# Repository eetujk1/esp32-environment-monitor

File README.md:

# ESP32 Environment Monitor

A custom-designed environmental monitoring board based on the ESP32-WROOM-32E-N4.

The goal of this project is to build a compact device for monitoring room temperature and relative humidity, with the possibility of expanding it into a Wi-Fi-connected monitoring system.

## Overview

The PCB integrates the main controller, sensor interface, USB programming circuitry, and power regulation into a single board.

## PCB Design

### 3D View

### PCB Layout

## Hardware

* **MCU:** ESP32-WROOM-32E-N4
* **Sensor:** DHT20
* **USB-to-UART:** CH340C
* **Voltage regulator:** AP2112K-3.3
* **Power input:** USB-C, 5 V
* **Programming:** Automatic boot mode selection with BOOT and RESET buttons
* **Sensor interface:** I²C

## Design Goals

* Custom PCB design and assembly
* Reliable temperature and humidity measurements
* Simple USB-based firmware development
* Wi-Fi connectivity for future monitoring applications
* Expandable hardware and firmware architecture

## Development Status

| Area                         | Status         |
| ---------------------------- | -------------- |
| PCB design                   | Completed      |
| PCB assembly                 | Pending        |
| Firmware                     | In development |
| Sensor validation            | Pending        |

## Planned Development

1. Bring up the hardware and verify the 3.3 V power rail.
2. Test USB communication and ESP32 firmware uploading.
3. Implement DHT20 sensor readings over I²C.
4. Validate temperature and humidity measurements.
5. Explore Wi-Fi monitoring and data visualization.

## Repository Structure

```text
esp32-environment-monitor/
├── hardware/       # PCB and schematic files
├── firmware/       # ESP32 source code
├── docs/           # Design notes and documentation
└── README.md
```

## Project Notes

This project is currently in the hardware bring-up stage. Firmware, measurements, and additional documentation will be added as development progresses.

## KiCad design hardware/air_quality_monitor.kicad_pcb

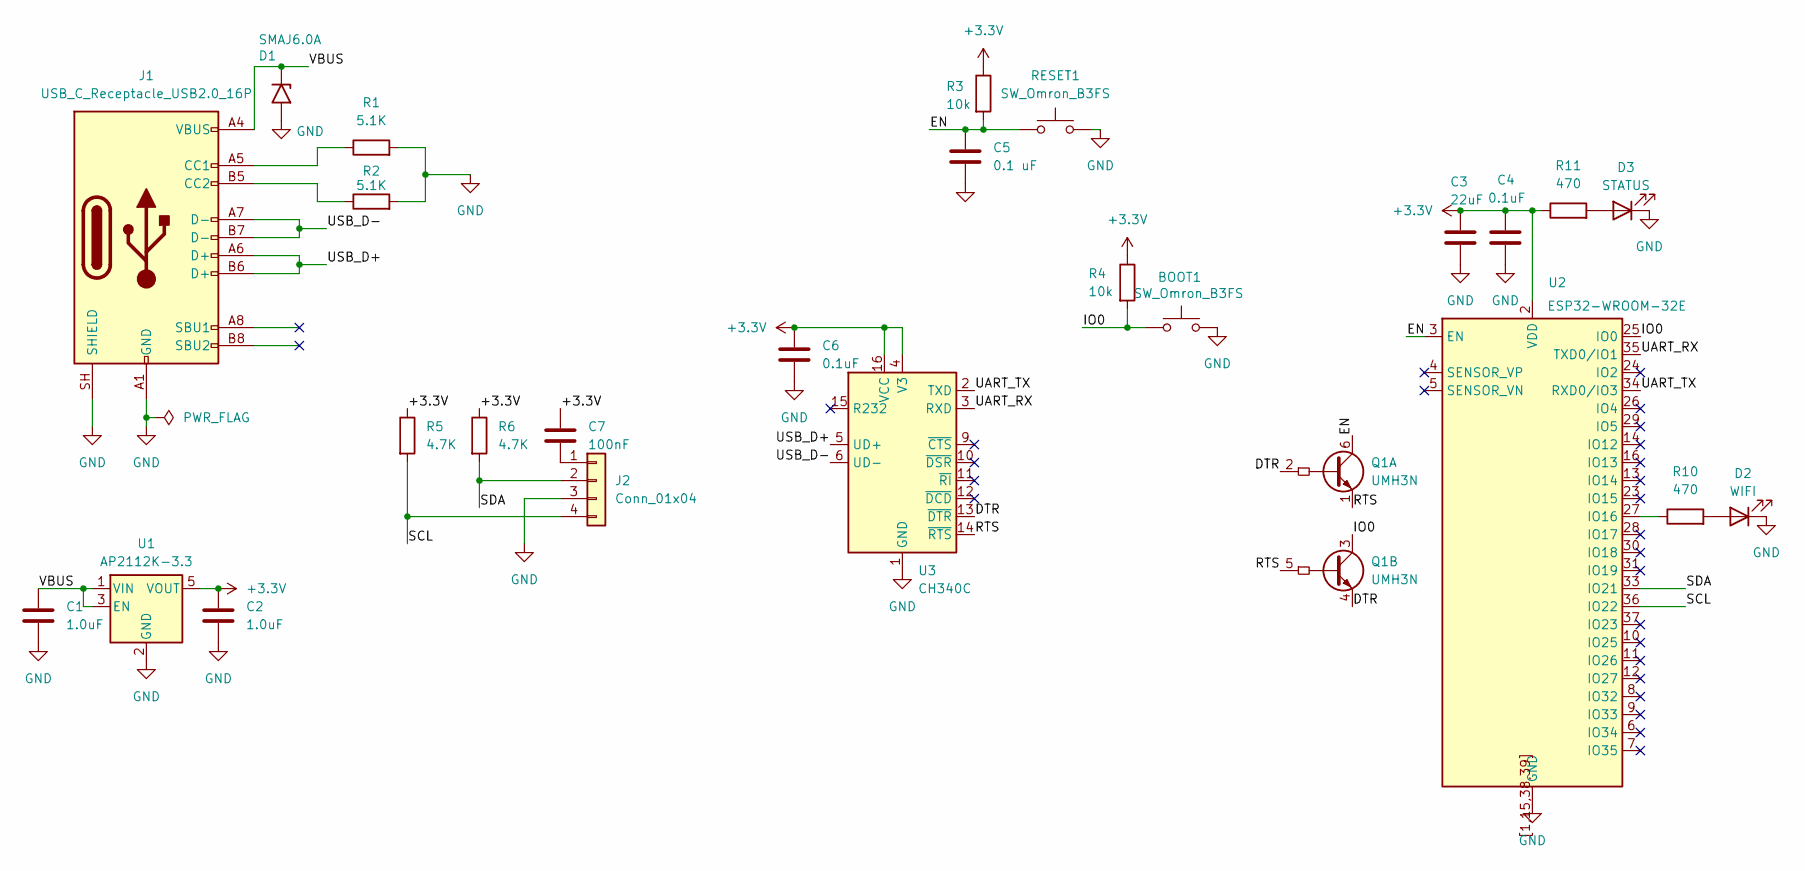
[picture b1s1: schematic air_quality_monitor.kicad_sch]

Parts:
BOOT1: SW_Omron_B3FS; SW_SPST_Omron_B3FS-105xP
C1, C2: 1.0uF; C_0805_2012Metric_Pad1.18x1.45mm_HandSolder
C3: 22uF; C_0805_2012Metric_Pad1.18x1.45mm_HandSolder
C4, C6: 0.1uF; C_0805_2012Metric_Pad1.18x1.45mm_HandSolder
C5: 0.1 uF; C_0805_2012Metric_Pad1.18x1.45mm_HandSolder
C7: 100nF; C_0805_2012Metric_Pad1.18x1.45mm_HandSolder
D1: SMAJ6.0A; D_SMA_Handsoldering
D2: WIFI; LED_0805_2012Metric_Pad1.15x1.40mm_HandSolder
D3: STATUS; LED_0805_2012Metric_Pad1.15x1.40mm_HandSolder
J1: USB_C_Receptacle_USB2.0_16P; USB_C_Receptacle_GCT_USB4105-xx-A_16P_TopMnt_Horizontal
J2: Conn_01x04; PinHeader_1x04_P2.54mm_Vertical
Q1: UMH3N; SOT-363_SC-70-6
R1, R2: 5.1K; R_0805_2012Metric_Pad1.20x1.40mm_HandSolder
R3, R4: 10k; R_0805_2012Metric_Pad1.20x1.40mm_HandSolder
R5, R6: 4.7K; R_0805_2012Metric
R10, R11: 470; R_0805_2012Metric_Pad1.20x1.40mm_HandSolder
RESET1: SW_Omron_B3FS; SW_SPST_Omron_B3FS-105xP
U1: AP2112K-3.3; SOT-23-5
U2: ESP32-WROOM-32E
U3: CH340C; SOIC-16_3.9x9.9mm_P1.27mm

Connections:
+3.3V: C2.1, C3.1, C4.1, C6.1, C7.1, R3.1, R4.1, R5.1, R6.1, R11.1, U1.5 (VOUT), U2.2 (VDD), U3.4 (V3), U3.16 (VCC)
/DTR: Q1.2 (B1), Q1.4 (E2), U3.13 (~DTR)
/EN: C5.1, Q1.6 (C1), R3.2, RESET1.1, U2.3 (EN)
/IO0: BOOT1.1, Q1.3 (C2), R4.2, U2.25 (IO0)
/RTS: Q1.1 (E1), Q1.5 (B2), U3.14 (~RTS)
/SCL: J2.4, R5.2, U2.36 (IO22)
/SDA: J2.2, R6.2, U2.33 (IO21)
/UART_RX: U2.35 (TXD0/IO1), U3.3 (RXD)
/UART_TX: U2.34 (RXD0/IO3), U3.2 (TXD)
/USB_D+: J1.A6 (D+), J1.B6 (D+), U3.5 (UD+)
/USB_D-: J1.A7 (D-), J1.B7 (D-), U3.6 (UD-)
/VBUS: C1.2, D1.1 (A1), J1.A4 (VBUS), J1.A9 (VBUS), J1.B4 (VBUS), J1.B9 (VBUS), U1.1 (VIN), U1.3 (EN)
GND: BOOT1.2, C1.1, C2.2, C3.2, C4.2, C5.2, C6.2, D1.2 (A2), D2.1 (K), D3.1 (K), J1.A1 (GND), J1.A12 (GND), J1.B1 (GND), J1.B12 (GND), J1.SH (SHIELD), J2.3, R1.2, R2.2, RESET1.2, U1.2 (GND), U2.1 (GND), U2.15 (GND), U2.38 (GND), U2.39 (GND), U2.[1,15,38,39] (GND), U3.1 (GND)
unnamed: D2.2 (A), R10.2
unnamed: D3.2 (A), R11.2
unnamed: J1.A5 (CC1), R1.1
unnamed: J1.B5 (CC2), R2.1
unnamed: C7.2, J2.1
unnamed: R10.1, U2.27 (IO16)

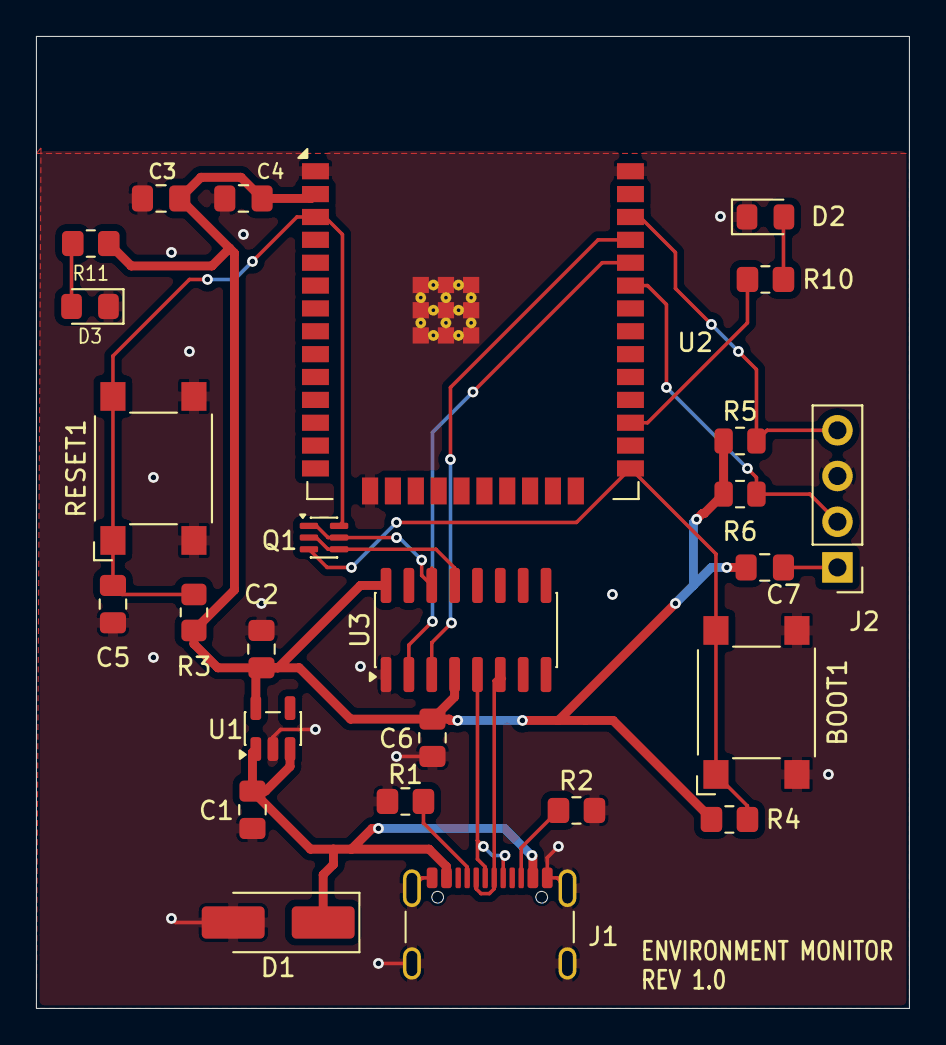
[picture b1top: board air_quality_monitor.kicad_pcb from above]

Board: 2 copper layers, 48.5 x 54.0 mm, 26 parts (0 on the bottom side), 19 nets.
